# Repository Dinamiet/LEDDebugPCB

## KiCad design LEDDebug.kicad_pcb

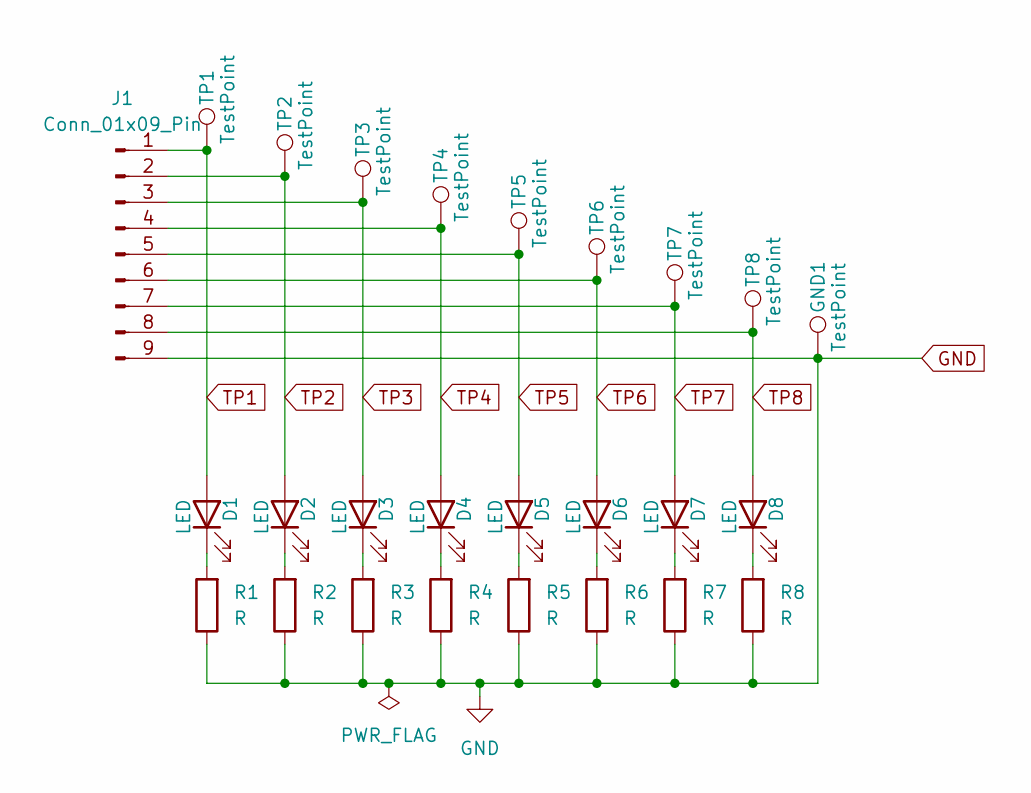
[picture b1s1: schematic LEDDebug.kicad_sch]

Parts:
D1, D2, D3, D4, D5, D6, D7, D8: LED; LED_1206_3216Metric_Pad1.42x1.75mm_HandSolder
GND1: TestPoint; TestPoint_THTPad_D1.5mm_Drill0.7mm
J1: Conn_01x09_Pin; PinHeader_1x09_P2.54mm_Vertical
R1, R2, R3, R4, R5, R6, R7, R8: R; R_1206_3216Metric_Pad1.30x1.75mm_HandSolder
TP1, TP2, TP3, TP4, TP5, TP6, TP7, TP8: TestPoint; TestPoint_THTPad_D1.5mm_Drill0.7mm

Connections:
GND: GND1.1, J1.9, R1.1, R2.1, R3.1, R4.1, R5.1, R6.1, R7.1, R8.1
unnamed: D1.1 (K), R1.2
unnamed: D2.1 (K), R2.2
unnamed: D3.1 (K), R3.2
unnamed: D4.1 (K), R4.2
unnamed: D5.1 (K), R5.2
unnamed: D6.1 (K), R6.2
unnamed: D7.1 (K), R7.2
unnamed: D8.1 (K), R8.2
TP1: D1.2 (A), J1.1, TP1.1
TP2: D2.2 (A), J1.2, TP2.1
TP3: D3.2 (A), J1.3, TP3.1
TP4: D4.2 (A), J1.4, TP4.1
TP5: D5.2 (A), J1.5, TP5.1
TP6: D6.2 (A), J1.6, TP6.1
TP7: D7.2 (A), J1.7, TP7.1
TP8: D8.2 (A), J1.8, TP8.1

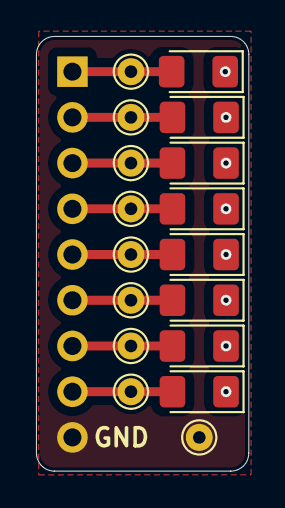
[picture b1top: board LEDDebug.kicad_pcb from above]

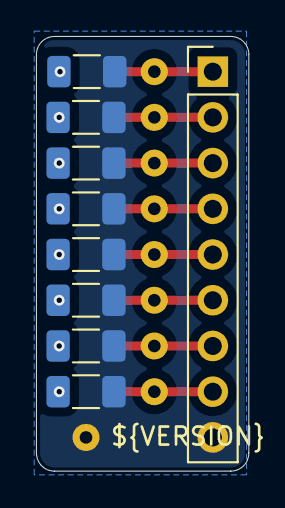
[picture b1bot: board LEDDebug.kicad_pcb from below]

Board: 2 copper layers, 11.8 x 24.1 mm, 26 parts (9 on the bottom side), 17 nets.

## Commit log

2024-12-23 Simple board layout
2024-12-23 Ignore KiCad unnecessary project files, backup files
2025-03-14 Add GitHub Sponsor configuration
2025-05-20 Component sizing and placement update
2025-06-05 Setup constraints
2025-07-04 Rounded PCB corners
2025-07-04 Version to PCB silkscreen
2025-07-04 Update Plot settings
